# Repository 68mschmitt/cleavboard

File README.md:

# Cleaver keyboard

A keyboard for my best tantrum buddy Cleaver: 117 hot-swap MX keys, with RGB and
single-color lighting variants.

## Current revision: 0.11

**[PCB fabrication package](designs/module-rp2040/manufacturing/rev0.11/README.md)** ·
**[Case, switch plate and assembly guide](designs/module-rp2040/mechanical/rev0.11/README.md)**

The PCB screws to the underside of the switch plate, then the combined assembly
slides over tall base posts and screws into the base. A replaceable USB-C bezel
lets the cable opening be fitted after assembling the actual controller.
The case retains its lower 3° profile, hidden cover screws and captured badge.
Use the **rev0.11 PCB, plate, base and cover together**.

## Revision 0.9 showcase (historical)

The earlier **[rev0.9](designs/module-rp2040/manufacturing/rev0.9/README.md)** introduced a
**2 × 1 inch [replaceable illuminated logo](designs/module-rp2040/LOGO.md)** between
the front three-key clusters, with matching rectangular plate/cover openings
and an 8 mm deeper front bezel.

Rendered from the actual rev0.9 case, populated PCB, switch plate and removable
badge, with all 117 switches, modeled keycaps, stabilizers and mounting hardware.
Colors, keycap profiles and logo illumination are illustrative; the sample “C”
glows cyan while per-key RGB is off.
[Full-resolution render and reproduction details](designs/module-rp2040/mechanical/rev0.9/case/renderings/README.md).

| Feature | Revision 0.9 |
| --- | --- |
| Layout | 117 keys: full-size typing area, numpad, navigation/arrow cluster, left macro column and extra front macro keys |
| Switches | Hot-swap MX, Cherry-compatible **plate-mount stabilizers**, 6.25u spacebar |
| Controller | **Waveshare RP2040-Plus 4MB**, removable via underside SMT sockets; right-facing USB-C |
| Lighting | **117 per-key + 4 logo RGB LEDs**, reverse-mounted; protected USB LED supply |
| Replaceable logo | **50.8 × 25.4 mm badge**, printed light well, 51.2 × 25.8 mm plate/cover openings; QMK/Vial color control |
| Firmware | **QMK / Vial**, with key remapping, macros and RGB control; default and Vial UF2 builds included |
| Enclosure | **5° rear-raised case**, 11 M2 PCB standoffs, controller-socket backstops, removable cover and USB-C opening |
| Dimensions | PCB: **452.44 × 147.64 × 1.6 mm**; case base: approximately **466 × 172 mm** |

### Build and explore

- **Current mechanics:** [rev0.11 cartridge and USB bezel](designs/module-rp2040/mechanical/rev0.11/README.md),
  including STL/STEP, FreeCAD assembly, mounting plan and fit coupons.
- **Electronics:** [design and assembly guide](designs/module-rp2040/README.md),
  [rev0.11 fabrication package, BOM and placement files](designs/module-rp2040/manufacturing/rev0.11/README.md).
- **Earlier mechanics:** [rev0.10 case for the rev0.9 PCB](designs/module-rp2040/mechanical/rev0.10/README.md).
- **Firmware:** [ready-to-flash UF2 files and instructions](designs/module-rp2040/manufacturing/rev0.9/firmware/README.md),
  [firmware source and configuration](designs/module-rp2040/firmware/README.md).
- **Look inside:** [populated PCB previews](designs/module-rp2040/previews/README.md),
  [current mounting plan](designs/module-rp2040/mechanical/rev0.11/case/mounting-plan.svg),
  [recorded validation and remaining prototype checks](designs/module-rp2040/VALIDATION.md).

> **Prototype status:** Electrical/layout checks and firmware builds have recorded
> passing results; physical hardware operation and case fit remain unverified.
> Print the fit coupons first. The case and plate are full-size, unsplit parts;
> the case needs approximately a 466 × 175 mm print area **plus brim clearance**.
> Use the specified long module headers and matching rev0.11 PCB/base/plate/cover. JLCPCB
> engineering/placement approval and physical socket mating remain required.

## Choose a hardware design

| Design | Open in KiCad | Documentation |
| --- | --- | --- |
| **Module RP2040 — rev0.11:** socketed RP2040-Plus, removable PCB/plate cartridge, adjustable USB bezel and illuminated badge | [Cleaver.kicad_pro](designs/module-rp2040/Cleaver.kicad_pro) | [Design and assembly](designs/module-rp2040/README.md), [manufacturing](designs/module-rp2040/manufacturing/README.md) |
| **Embedded RP2040 — embedded-0.2:** onboard RP2040 and USB-C, per-key RGB | [Cleaver-Embedded.kicad_pro](designs/embedded-rp2040/Cleaver-Embedded.kicad_pro) | [Design and status](designs/embedded-rp2040/README.md), [handoff](designs/embedded-rp2040/HANDOFF.md) |
| **Single-color devboard — white-0.1:** YD-RP2040 module, white backlight | [Cleaver-White.kicad_pro](designs/single-color-devboard/Cleaver-White.kicad_pro) | [Design and status](designs/single-color-devboard/README.md), [manufacturing](designs/single-color-devboard/manufacturing/README.md) |

Each design owns its KiCad libraries, firmware, generation tools, validation,
and manufacturing files. Read its documentation for revision and prototype status.

## Repository layout

```text
assets/                        Shared layout inputs and silkscreen artwork
designs/
  module-rp2040/               Original RGB module design, mechanics and releases
  embedded-rp2040/             Integrated-controller RGB design
  single-color-devboard/       Module-based white-backlight design
docs/                          Repository organization and path migration guide
tools/                         Cross-design utilities and repository checks
```

- [Design comparison](designs/README.md)
- [Repository structure and file-placement conventions](docs/REPOSITORY.md)
- [Original keyboard layout](assets/layout/README.md)
- [Taviana artwork, previews and recorded checks](assets/artwork/taviana/README.md)
- [Tools and verification commands](tools/README.md)

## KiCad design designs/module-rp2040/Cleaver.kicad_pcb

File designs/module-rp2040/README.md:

# Cleaver PCB — revision 0.11

**New: [replaceable illuminated logo](LOGO.md)** between M6–M8 and M9–M11.
Four RGB LEDs illuminate a **50.8 × 25.4 mm (2 × 1 inch)** printed badge through
matching **51.2 × 25.8 mm** plate/cover openings. The front bezel and plate extend
8 mm forward, preserving key positions. The light well and flanged insert lift
out when the cover is removed. The 121-pixel rev0.9 firmware remains compatible.

**New mounting arrangement:** use the [rev0.11 PCB, switch plate, base and cover](mechanical/rev0.11/README.md)
together. Twelve large PCB holes pass over tall base posts; twelve separate
underside screws attach the PCB to downward plate bosses. The assembled cartridge
then screws to the base from above. A replaceable USB bezel is fitted after
measuring the actual controller. The lower 3° profile, hidden cover screws and
anti-rattle badge retention carry forward.

**Taviana Tactical artwork:** the active PCB includes a 34 mm-wide top-side logo.
Use the current [revision 0.11 fabrication files](manufacturing/rev0.11/).

117 MX hot-swap switches, 121 reverse-mount RGB LEDs, and the **Waveshare
RP2040-Plus 4MB USB-C module** (bare SKU 20290), plugged into underside SMT
bottom-entry sockets. The keyboard is
USB-powered, with **no mechanical power switch** and no separate power supply.

Read [VALIDATION.md](VALIDATION.md) for the recorded checks and remaining prototype
tests. The old [DESIGN_REVIEW.md](DESIGN_REVIEW.md) describes revision 0.2, not this
replacement design. Electrical checks do not substitute for a physical prototype
or final plate/case checks.

**Revision 0.11 manufacturing:** all **489 factory-populated parts are underside
SMD**, including C5, the HanElectricity hot-swap sockets and **J1/J2 Harwin
M20-7862042 controller sockets**. U1 plugs in from above through 40 **NPTH**
holes. Solder two **Samtec TSW-120-14-G-S** strips to the module only: 8.13 mm
posts down, 2.79 mm tails through the module. Stock pre-headered SKU 20808 is
**not qualified**. See the [socket drawing, pin budget and production gates](references/CONTROLLER-SOCKETS-0.7.md).
TP1 is a bare underside VBUS test pad.
There are **twelve Ø7 mm post passages and twelve Ø2.2 mm attachment holes**,
five labelled underside probe pads and three bottom fiducials.
Use [`manufacturing/rev0.11/`](manufacturing/rev0.11/) for the purchasing BOM,
corrected socket placement data and fabrication package; use
[`mechanical/`](mechanical/) for the matching stabilizer/switch plate and
case mounting references. **Allow 11 mm clearance under C5**; the old case-depth
assumption no longer applies there. The [rev0.11 case base](mechanical/rev0.11/case/README.md)
includes socket-insertion backstops. Older Gerbers and placement exports are not
this revision. Original-part evidence remains in the [component review](references/COMPONENT-REVIEW.md);
new socket evidence is linked above. Supplier DFM and physical mating remain open.

## USB LED power through pin 40

The Waveshare **pin 40 is raw USB VBUS**, connected directly to the USB-C power
pins ahead of its VSYS isolation diode. A **0.6 mm PCB route** connects J2.1 (U1.40) to
the existing protected LED branch. **No module modification or tap wire is needed.**
TP1 at `(446, 27)` mm is retained as a VBUS test pad; TP3 measures the same net.
Ground returns through the module's ordinary GND header pins.

Use an RP2040-Plus for this revision: the former YD-RP2040 has diode-fed Vout at
pin 40 and is not a suitable substitute. Leave the Waveshare battery connector
unused for this USB-only keyboard.

LED power path:

```text
Module USB VBUS pin 40 → carrier copper → F1 (0.50 A PTC) → U3 (TPS2553) → LED_5V
Module GPIO28 → U3 enable (100 kΩ default-off pull-down)
Module GPIO27 → U2 level translator → R1 (330 Ω) → first LED DIN
```

- U3's **75 kΩ, 1%** current-limit resistor gives approximately **353 mA nominal**
  LED-branch current limiting (about **311–401 mA** using the datasheet bounds and
  resistor tolerance). This is separate from the module's own consumption.
- Firmware caps key brightness at **8/255**, with four badge pixels capped at
  **32/255**. For 12 mA/colour LEDs, combined full-white colour current is
  approximately **150.2 mA**, plus LED idle current and MCU
  consumption. Measure the actual total; a brightness setting or USB descriptor is
  not itself a current measurement. Do not raise the cap casually.
- RGB power stays off until USB is configured, and is removed on suspend and when
  RGB Matrix is disabled. R2 keeps it off during reset/bootloader operation.
- Every LED has its own 100 nF capacitor. C2 is 22 µF; **C5 is a low-impedance
  470 µF reservoir after the current limiter**, to supply coincident LED PWM pulses.
  It is not attached directly across USB at cable insertion. Fit its polarity
  correctly: pad 1 / `+` is positive, and the can's negative mark goes to pad 2.
- U2 is **SN74LV1T125DBVR**, not an arbitrary 74LVC/HC/AHCT substitute. Its
  reduced input thresholds translate 3.3 V data to the LED supply, and its input
  tolerates the GPIO while the LED supply is off.
- TP1 is connected to USB VBUS, not a separate power input.

## Controller placement and pinout

The module uses two 20-pin, 2.54 mm-pitch headers **17.78 mm apart**. Its body is
**51 × 21 mm**, based on Waveshare's mechanical drawing. It sits
top-right, USB-C facing the right edge. Header centres are retained from rev0.5;
the smaller body ends **1.17 mm inside** the carrier edge, with the USB-C shell
projecting beyond the module body. Use headers/sockets with sufficient
underside clearance, and confirm the actual purchased board against a 1:1 print.

The module uses **Pico-compatible numbering**, not alternating 2×20 numbering.
J1.1–20 carry module pins 1–20; **J2.1–20 carry module pins 40–21**, respectively.
The 7.5 mm female socket bodies sit below the carrier; male-header insulators
seat on top. The module is not raised by a top-side female header stack.

| Module pin | RP2040-Plus function | Carrier use |
| --- | --- | --- |
| 35 | ADC_VREF | Unconnected |
| 36 | 3V3_OUT | Unconnected |
| 37 | 3V3_EN | Unconnected; module pull-up keeps regulator enabled |
| 38 | GND | Ground plane |
| 39 | VSYS | Unconnected |
| 40 | USB VBUS | RAW_USB_5V → F1 → U3 → LED_5V |

The module's BOOT and RESET buttons remain accessible in the upper-right area.
No separate USB connector or USB data traces are required on the carrier.

## Matrix, RGB order, and assembly

The electrical matrix is **8×16 ROW2COL**, with 117 unique populated cells:

| Function | GPIOs |
| --- | --- |
| Rows 0–7 | GP0–GP7 |
| Columns 0–15 | GP8–GP22, GP26 |
| RGB data | GP27 |
| RGB power enable | GP28 |

Logical rows are banks of 16 switches in KLE order, **not** the seven physical
key rows. This avoids the old duplicate addresses without adding an expander.
Vial still displays the original physical layout. Every switch goes from its row
through the switch to the diode anode; the cathode connects to the column.

- Diodes are **1N4148W, SOD-123**, using normal **pad 1 = cathode, pad 2 = anode**
  numbering. Match the diode's stripe to the footprint's cathode mark.
  Diodes sit 8.25 mm above switch centres, improving body clearance to sockets.
  These and all other SMD parts are factory-assembled underneath.
- LEDs use the **OPSCO SK6812MINI-E / C5149201 catalog pinout**:
  **1=GND, 2=DIN, 3=VDD, 4=DOUT**. This renumbers the older Rev.02 sheet's pins
  without changing physical net positions. Do not substitute MINI/EA/5050
  packages based only on a similar name.
- LEDs and their 0805 bypass capacitors are on **B.Cu**, with emitters facing
  through the **3.6 × 3.2 mm PCB openings toward the switches**. These are real
  Edge.Cuts, not reference artwork. Mounting pads are outside the opening and
  retain at least 0.5 mm nominal edge clearance.
  From the **top/emitter side**, pad 3 is upper-left, pad 4 lower-left, pad 1
  lower-right, and pad 2 upper-right. The ground-corner mark is on the back.
  Check this orientation on one LED before assembling the entire chain.
  Specify an internal milling-corner radius **no larger than 0.5 mm** (prefer
  0.4 mm) for these small openings; a default 2 mm-diameter cutter will not fit
  the LED's square corners. Confirm the fabricator's aperture tolerances.
- The chain begins at the function-row Pause key near the MCU circuitry, runs
  left across that row, and then snakes across subsequent physical rows. Firmware
  entries are in **actual chain order**, not switch-reference order.
  LED118–LED121 append after LED112 (M6), at indices 117–120, and illuminate the
  badge. C218–C221 are their bypass capacitors. [Badge circuit and controls](LOGO.md#rgb-and-power).
- `firmware/key_matrix.csv` gives switch, matrix cell, position, and RGB index.
  `manufacturing/BOM.csv` lists exact references, values, board side, and placement coordinates.
  SWxxx, Dxxx, and LEDxxx refer to the same physical key; C101 belongs to SW001.
  Each SW footprint is a **B.Cu HanElectricity CPG151101S11-16 / C41430893 socket**.
  The switch plugs in from above. Its origin is still the switch centre; use the
   revision-specific factory CPL for the actual socket placement centre. The owner
   provides the bare RP2040-Plus and two **TSW-120-14-G-S** male strips, soldered
   only to the module. J1/J2 female sockets are factory-fitted underneath.
   Leave all carrier entry holes open and solder-free.
- Caps/Num/Scroll lock are indicated using their **own keys' RGB LEDs**. The three
  decorative KLE circles above the numpad do not represent additional components
hidden beneath the MCU.

The four-layer stack uses In1.Cu as ground return, with explicit ground vias
outside solder pads. A **switched LED_5V pour on F.Cu** and off-pad power vias
feed each LED and bypass capacitor, avoiding a narrow, serial supply chain.
Signals use F.Cu/In2.Cu/B.Cu. Preferred track widths are
0.3 mm for signals and 0.6 mm for power; manufacturing minima remain 0.2 mm track,
0.2 mm clearance, 0.5 mm copper-to-edge, and the existing project hole rules.
Ordinary through-vias are used; filled/capped via-in-pad fabrication is not needed.

The power/buffer circuit and bulk capacitor occupy the empty region **left of
the MCU**, rather than overlapping its body or headers. C5 is a bottom-mounted
**Nichicon PCF1A471MCL1GS / C3275369**, 470 µF/10 V SMD polymer, Ø10 mm and
10 mm maximum height, centred at `(377, 6)` mm. Allow **11 mm free case depth
below the PCB at C5**. The old top capacitor plate opening can remain unused.

**Mechanical interface:** switch centres and board outline are retained. The
new plate in `mechanical/` includes matching M2 holes and Cherry-style
**plate-mount stabilizers**: seven 2u sets and one 6.25u spacebar set. Do not use
PCB-mount stabilizers. The custom printed case uses the supplied hole-coordinate
table and 6 mm screw/standoff envelopes. See the mechanical README for nominal
plate spacing, clip thickness, controller/capacitor openings and a fit coupon.

## Populated 3D view

Open **Cleaver.kicad_pcb → View → 3D Viewer (Alt+3)**. The project includes local
models for **all 490 populated/modelled footprints**, including front-side MX switches,
back-side sockets, LEDs/passives, and a simplified RP2040-Plus with long headers/USB-C.
The controller sockets have nominal supplier-dimensioned STEP/VRML models.
No extra model-library installation is needed. Flip the view with **F** to see
the underside. TP1–TP6, mounting holes and fiducials intentionally have no models.

- [Historical rev0.7 top-side preview](previews/Cleaver-rev0.7-top.png)
- [Historical rev0.7 bottom-side preview](previews/Cleaver-rev0.7-bottom.png)
- [Model coverage, approximations, licensing, and STEP export](Cleaver.3dshapes/README.md)

The module/header stack and some package details are approximations; keycaps,
plate, stabilizers, and case are not modeled. These views do not replace the
physical fit checks above. Model assignments are preserved by the generator.

## Vial-QMK firmware

Pin assignments are unchanged; revision 0.9 builds drive all 121 LEDs. Images and
instructions are in [`manufacturing/rev0.9/firmware/`](manufacturing/rev0.9/firmware/).

Copy `firmware/` to `keyboards/cleaver/` in a **vial-qmk** checkout. From that
checkout run:

```sh
make cleaver:default
make cleaver:vial
```

The Vial keymap includes its own UID, physical `vial.json`, VIA/Vial/VialRGB rules,
and a secure **Esc + main Enter** unlock combination. No insecure-unlock option is
enabled. The RP2040 vendor/PIO WS2812 driver uses GRB data and explicit timings.
The module's onboard GP25 status LED is not included in the keyboard's 121-LED chain.
Default macro-key assignments can be changed in Vial.

All 26 carrier GPIOs retain their physical pin numbers. The Vial UID, VID/PID,
layout, unlock combination, first 117 RGB indices and USB-aware GP28 power control
are retained. Four non-key badge pixels extend the chain. QMK's default
W25Q080-compatible boot stage supports the module's
W25Q32JV flash. EEPROM remains explicitly within the first 2MB, also valid on
the 16MB RP2040-Plus variant. See [`firmware/README.md`](firmware/README.md).

Build provenance and the tested vial-qmk commit belong in [VALIDATION.md](VALIDATION.md).
Compiled firmware has not been exercised on a physical keyboard by this agent.

## Regeneration and checks

`source/design.py` is the shared source for schematic, PCB nets, matrix, RGB
order, and firmware. The PCB receives pad nets from **KiCad's exported schematic
netlist**. Regeneration preserves project settings except for the explicit power
netclass and the preferred 0.3 mm signal width; it does not weaken DRC minima.

Run the following commands from the repository root with KiCad's Python environment.

Generate a fresh **unrouted** placement and DSN only when deliberately restarting
routing:

```sh
python3 -B designs/module-rp2040/source/generate_kicad.py --placement-only
```

Import a matching routed Specctra session:

```sh
python3 -B designs/module-rp2040/source/generate_kicad.py --ses designs/module-rp2040/routing/Cleaver.ses
python3 -B designs/module-rp2040/source/check_kicad.py
python3 -B -m unittest discover -s designs/module-rp2040/source -p 'test_*.py'
```

See `routing/README.md` for the autorouter invocation. The DSN preparation carries
KiCad's edge clearances and power widths into the router; a router reporting
“0 violations” is **not** a substitute for KiCad DRC after session import.

## Hardware sources

- [Waveshare RP2040-Plus documentation](https://docs.waveshare.com/RP2040-Plus).
- [Archived module schematic](references/RP2040-Plus-schematic.pdf),
  [dimension drawing](references/RP2040-Plus-dimensions.webp), and
  [source/pinout review](references/RP2040-Plus.md).
- [OPSCO C5149201 datasheet](https://datasheet.lcsc.com/datasheet/pdf/0907a34a701b4aef568078003f6e9eae.pdf).
  Physical reverse-mount signal orientation also agrees with the
  [established MX MINI-E footprint](https://github.com/ebastler/kicad-keyboard-parts.pretty/blob/master/MX_SK6812MINI-E.kicad_mod).
- [SN74LV1T125](https://www.ti.com/lit/ds/symlink/sn74lv1t125.pdf),
  [TPS2553](https://www.ti.com/lit/ds/symlink/tps2553.pdf), and
  [Nichicon PCF capacitor specification](references/Nichicon-PCF.pdf).
- [Exact-part JLCPCB review and socket compatibility](references/COMPONENT-REVIEW.md).

Fit the carrier to its socket-support base **before inserting U1**; the 40
contacts can require substantial force. Withdraw evenly, never by levering the
USB shell. Print the new USB/seat coupons first.

Bring up the prototype on current-limited USB power: check supply polarity/shorts,
test the module and one key first, then one LED, all 117 keys (including chords),
the complete RGB chain, maximum allowed full-white current/rail ripple,
suspend/resume, and USB-A-to-C plus C-to-C enumeration. Keep the brightness cap
until those measurements pass.

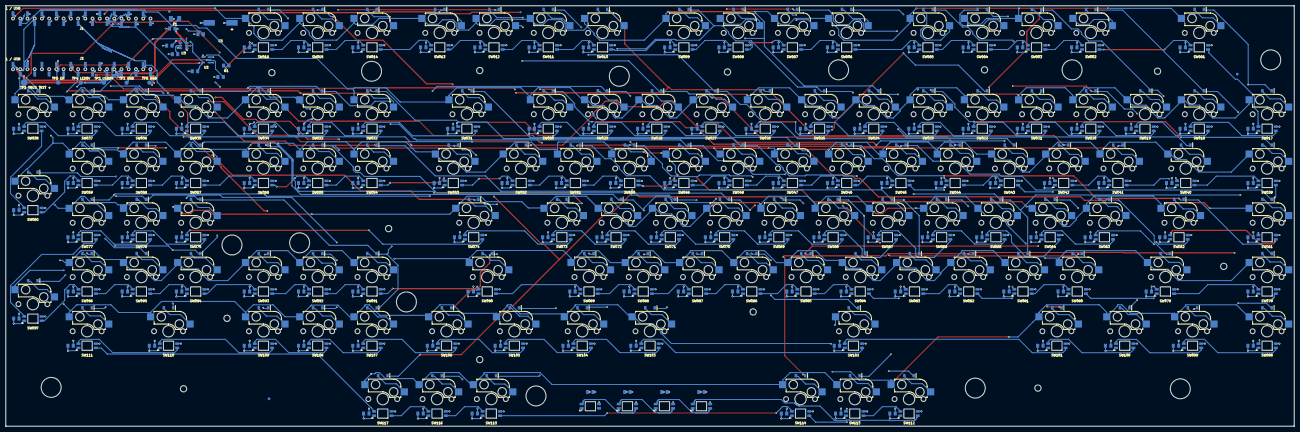
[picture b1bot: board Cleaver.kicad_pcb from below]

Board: 4 copper layers, 452.4 x 147.6 mm, 524 parts (498 on the bottom side), 270 nets.

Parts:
C1: 1uF 50V X7R; C_0805
C2: 22uF 10V X5R; C_0805
C3, C101, C102, C103, C104, C105, C106, C107, C108, C109, C110, C111, C112, C113, C114, C115, C116, C117, C118, C119, C120, C121, C122, C123, C124, C125, C126, C127, C128, C129, C130, C131, C132, C133, C134, C135, C136, C137, C138, C139, C140, C141, C142, C143, C144, C145, C146, C147, C148, C149, C150, C151, C152, C153, C154, C155, C156, C157, C158, C159, C160, C161, C162, C163, C164, C165, C166, C167, C168, C169, C170, C171, C172, C173, C174, C175, C176, C177, C178, C179, C180, C181, C182, C183, C184, C185, C186, C187, C188, C189, C190, C191, C192, C193, C194, C195, C196, C197, C198, C199, C200, C201, C202, C203, C204, C205, C206, C207, C208, C209, C210, C211, C212, C213, C214, C215, C216, C217, C218, C219, C220, C221: 100nF 50V X7R; C_0805
C5: 470uF 10V PCF1A471MCL1GS; C_PCF_D10
D001, D002, D003, D004, D005, D006, D007, D008, D009, D010, D011, D012, D013, D014, D015, D016, D017, D018, D019, D020, D021, D022, D023, D024, D025, D026, D027, D028, D029, D030, D031, D032, D033, D034, D035, D036, D037, D038, D039, D040, D041, D042, D043, D044, D045, D046, D047, D048, D049, D050, D051, D052, D053, D054, D055, D056, D057, D058, D059, D060, D061, D062, D063, D064, D065, D066, D067, D068, D069, D070, D071, D072, D073, D074, D075, D076, D077, D078, D079, D080, D081, D082, D083, D084, D085, D086, D087, D088, D089, D090, D091, D092, D093, D094, D095, D096, D097, D098, D099, D100, D101, D102, D103, D104, D105, D106, D107, D108, D109, D110, D111, D112, D113, D114, D115, D116, D117: 1N4148W; D_SOD123
F1: 1206L050YR 0.50A hold; PTC_1206
FID1, FID2, FID3: Fiducial
H1, H2, H3, H4, H5, H6, H7, H8, H9, H10, H11, H12: MountingHole_Post7
H13, H14, H15, H16, H17, H18, H19, H20, H21, H22, H23, H24: MountingHole_M2
J1, J2: M20-7862042; Harwin_M20_7862042
LED001, LED002, LED003, LED004, LED005, LED006, LED007, LED008, LED009, LED010, LED011, LED012, LED013, LED014, LED015, LED016, LED017, LED018, LED019, LED020, LED021, LED022, LED023, LED024, LED025, LED026, LED027, LED028, LED029, LED030, LED031, LED032, LED033, LED034, LED035, LED036, LED037, LED038, LED039, LED040, LED041, LED042, LED043, LED044, LED045, LED046, LED047, LED048, LED049, LED050, LED051, LED052, LED053, LED054, LED055, LED056, LED057, LED058, LED059, LED060, LED061, LED062, LED063, LED064, LED065, LED066, LED067, LED068, LED069, LED070, LED071, LED072, LED073, LED074, LED075, LED076, LED077, LED078, LED079, LED080, LED081, LED082, LED083, LED084, LED085, LED086, LED087, LED088, LED089, LED090, LED091, LED092, LED093, LED094, LED095, LED096, LED097, LED098, LED099, LED100, LED101, LED102, LED103, LED104, LED105, LED106, LED107, LED108, LED109, LED110, LED111, LED112, LED113, LED114, LED115, LED116, LED117, LED118, LED119, LED120, LED121: SK6812MINI-E C5149201; MINI_E
LOGO1: TavianaTactical_34mm
R1: 330R; R_0805
R2, R3: 100k; R_0805
R4: 75k 1%; R_0805
SW001, SW002, SW003, SW004, SW005, SW006, SW007, SW008, SW009, SW010, SW011, SW012, SW013, SW014, SW015, SW016, SW017, SW018, SW019, SW020, SW021, SW022, SW023, SW024, SW025, SW026, SW027, SW028, SW029, SW030, SW031, SW032, SW033, SW034, SW035, SW036, SW037, SW038, SW039, SW040, SW041, SW042, SW043, SW044, SW045, SW046, SW047, SW048, SW049, SW050, SW051, SW052, SW053, SW054, SW055, SW056, SW057, SW058, SW059, SW060, SW061, SW062, SW063, SW064, SW065, SW066, SW067, SW068, SW069, SW070, SW071, SW072, SW073, SW074, SW075, SW076, SW077, SW078, SW079, SW080, SW081, SW082, SW083, SW084, SW085, SW086, SW087, SW088, SW089, SW090, SW091, SW092, SW093, SW094, SW095, SW096, SW097, SW098, SW099, SW100, SW101, SW102, SW103, SW104, SW105, SW106, SW107, SW108, SW109, SW110, SW111, SW112, SW113, SW114, SW115, SW116, SW117: CPG151101S11-16; HanElectricity_CPG151101S11-16
TP1: USB VBUS TEST +5V; WirePad
TP2: GND; TestPad
TP3: RAW_USB_5V; TestPad
TP4: LED_5V; TestPad
TP5: LED_EN; TestPad
TP6: RGB_BUFFERED; TestPad
U1: Waveshare RP2040-Plus 4MB; Waveshare_RP2040_Plus
U2: SN74LV1T125DBVR; LV1T125
U3: TPS2553DBVR; TPS2553

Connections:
/COL00: D001.1, D017.1, D033.1, D049.1, D065.1, D081.1, D097.1, D113.1, J1.11
/COL01: D002.1, D018.1, D034.1, D050.1, D066.1, D082.1, D098.1, D114.1, J1.12
/COL02: D003.1, D019.1, D035.1, D051.1, D067.1, D083.1, D099.1, D115.1, J1.14
/COL03: D004.1, D020.1, D036.1, D052.1, D068.1, D084.1, D100.1, D116.1, J1.15
/COL04: D005.1, D021.1, D037.1, D053.1, D069.1, D085.1, D101.1, D117.1, J1.16
/COL05: D006.1, D022.1, D038.1, D054.1, D070.1, D086.1, D102.1, J1.17
/COL06: D007.1, D023.1, D039.1, D055.1, D071.1, D087.1, D103.1, J1.19
/COL07: D008.1, D024.1, D040.1, D056.1, D072.1, D088.1, D104.1, J1.20
/COL08: D009.1, D025.1, D041.1, D057.1, D073.1, D089.1, D105.1, J2.20
/COL09: D010.1, D026.1, D042.1, D058.1, D074.1, D090.1, D106.1, J2.19
/COL10: D011.1, D027.1, D043.1, D059.1, D075.1, D091.1, D107.1, J2.17
/COL11: D012.1, D028.1, D044.1, D060.1, D076.1, D092.1, D108.1, J2.16
/COL12: D013.1, D029.1, D045.1, D061.1, D077.1, D093.1, D109.1, J2.15
/COL13: D014.1, D030.1, D046.1, D062.1, D078.1, D094.1, D110.1, J2.14
/COL14: D015.1, D031.1, D047.1, D063.1, D079.1, D095.1, D111.1, J2.12
/COL15: D016.1, D032.1, D048.1, D064.1, D080.1, D096.1, D112.1, J2.10
/CURRENT_LIMIT: R4.1, U3.5
/FUSED_5V: C1.1, F1.2, U3.1
/GND: C1.2, C2.2, C3.2, C5.2, C101.2, C102.2, C103.2, C104.2, C105.2, C106.2, C107.2, C108.2, C109.2, C110.2, C111.2, C112.2, C113.2, C114.2, C115.2, C116.2, C117.2, C118.2, C119.2, C120.2, C121.2, C122.2, C123.2, C124.2, C125.2, C126.2, C127.2, C128.2, C129.2, C130.2, C131.2, C132.2, C133.2, C134.2, C135.2, C136.2, C137.2, C138.2, C139.2, C140.2, C141.2, C142.2, C143.2, C144.2, C145.2, C146.2, C147.2, C148.2, C149.2, C150.2, C151.2, C152.2, C153.2, C154.2, C155.2, C156.2, C157.2, C158.2, C159.2, C160.2, C161.2, C162.2, C163.2, C164.2, C165.2, C166.2, C167.2, C168.2, C169.2, C170.2, C171.2, C172.2, C173.2, C174.2, C175.2, C176.2, C177.2, C178.2, C179.2, C180.2, C181.2, C182.2, C183.2, C184.2, C185.2, C186.2, C187.2, C188.2, C189.2, C190.2, C191.2, C192.2, C193.2, C194.2, C195.2, C196.2, C197.2, C198.2, C199.2, C200.2, C201.2, C202.2, C203.2, C204.2, C205.2, C206.2, C207.2, C208.2, C209.2, C210.2, C211.2, C212.2, C213.2, C214.2, C215.2, C216.2, C217.2, C218.2, C219.2, C220.2, C221.2, J1.3, J1.8, J1.13, J1.18, J2.3, J2.8, J2.13, J2.18, LED001.1, LED002.1, LED003.1, LED004.1, LED005.1, LED006.1, LED007.1, LED008.1, LED009.1, LED010.1, LED011.1, LED012.1, LED013.1, LED014.1, LED015.1, LED016.1, LED017.1, LED018.1, LED019.1, LED020.1, LED021.1, LED022.1, LED023.1, LED024.1, LED025.1, LED026.1, LED027.1, LED028.1, LED029.1, LED030.1, LED031.1, LED032.1, LED033.1, LED034.1, LED035.1, LED036.1, LED037.1, LED038.1, LED039.1, LED040.1, LED041.1, LED042.1, LED043.1, LED044.1, LED045.1, LED046.1, LED047.1, LED048.1, LED049.1, LED050.1, LED051.1, LED052.1, LED053.1, LED054.1, LED055.1, LED056.1, LED057.1, LED058.1, LED059.1, LED060.1, LED061.1, LED062.1, LED063.1, LED064.1, LED065.1, LED066.1, LED067.1, LED068.1, LED069.1, LED070.1, LED071.1, LED072.1, LED073.1, LED074.1, LED075.1, LED076.1, LED077.1, LED078.1, LED079.1, LED080.1, LED081.1, LED082.1, LED083.1, LED084.1, LED085.1, LED086.1, LED087.1, LED088.1, LED089.1, LED090.1, LED091.1, LED092.1, LED093.1, LED094.1, LED095.1, LED096.1, LED097.1, LED098.1, LED099.1, LED100.1, LED101.1, LED102.1, LED103.1, LED104.1, LED105.1, LED106.1, LED107.1, LED108.1, LED109.1, LED110.1, LED111.1, LED112.1, LED113.1, LED114.1, LED115.1, LED116.1, LED117.1, LED118.1, LED119.1, LED120.1, LED121.1, R2.2, R3.2, R4.2, TP2.1, U2.1, U2.3, U3.2
/KEY000: D001.2, SW001.2
/KEY001: D002.2, SW002.2
/KEY002: D003.2, SW003.2
/KEY003: D004.2, SW004.2
/KEY004: D005.2, SW005.2
/KEY005: D006.2, SW006.2
/KEY006: D007.2, SW007.2
/KEY007: D008.2, SW008.2
/KEY008: D009.2, SW009.2
/KEY009: D010.2, SW010.2
/KEY010: D011.2, SW011.2
/KEY011: D012.2, SW012.2
/KEY012: D013.2, SW013.2
/KEY013: D014.2, SW014.2
/KEY014: D015.2, SW015.2
/KEY015: D016.2, SW016.2
/KEY016: D017.2, SW017.2
/KEY017: D018.2, SW018.2
/KEY018: D019.2, SW019.2
/KEY019: D020.2, SW020.2
/KEY020: D021.2, SW021.2
/KEY021: D022.2, SW022.2
/KEY022: D023.2, SW023.2
/KEY023: D024.2, SW024.2
/KEY024: D025.2, SW025.2
/KEY025: D026.2, SW026.2
/KEY026: D027.2, SW027.2
/KEY027: D028.2, SW028.2
/KEY028: D029.2, SW029.2
/KEY029: D030.2, SW030.2
/KEY030: D031.2, SW031.2
/KEY031: D032.2, SW032.2
/KEY032: D033.2, SW033.2
/KEY033: D034.2, SW034.2
/KEY034: D035.2, SW035.2
/KEY035: D036.2, SW036.2
/KEY036: D037.2, SW037.2
/KEY037: D038.2, SW038.2
/KEY038: D039.2, SW039.2
/KEY039: D040.2, SW040.2
/KEY040: D041.2, SW041.2
/KEY041: D042.2, SW042.2
/KEY042: D043.2, SW043.2
/KEY043: D044.2, SW044.2
/KEY044: D045.2, SW045.2
/KEY045: D046.2, SW046.2
/KEY046: D047.2, SW047.2
/KEY047: D048.2, SW048.2
/KEY048: D049.2, SW049.2
/KEY049: D050.2, SW050.2
/KEY050: D051.2, SW051.2
/KEY051: D052.2, SW052.2
/KEY052: D053.2, SW053.2
/KEY053: D054.2, SW054.2
/KEY054: D055.2, SW055.2
/KEY055: D056.2, SW056.2
/KEY056: D057.2, SW057.2
/KEY057: D058.2, SW058.2
/KEY058: D059.2, SW059.2
/KEY059: D060.2, SW060.2
/KEY060: D061.2, SW061.2
/KEY061: D062.2, SW062.2
/KEY062: D063.2, SW063.2
/KEY063: D064.2, SW064.2
/KEY064: D065.2, SW065.2
/KEY065: D066.2, SW066.2
/KEY066: D067.2, SW067.2
/KEY067: D068.2, SW068.2
/KEY068: D069.2, SW069.2
/KEY069: D070.2, SW070.2
/KEY070: D071.2, SW071.2
/KEY071: D072.2, SW072.2
/KEY072: D073.2, SW073.2
/KEY073: D074.2, SW074.2
/KEY074: D075.2, SW075.2
/KEY075: D076.2, SW076.2
/KEY076: D077.2, SW077.2
/KEY077: D078.2, SW078.2
/KEY078: D079.2, SW079.2
/KEY079: D080.2, SW080.2
/KEY080: D081.2, SW081.2
/KEY081: D082.2, SW082.2
/KEY082: D083.2, SW083.2
/KEY083: D084.2, SW084.2
/KEY084: D085.2, SW085.2
/KEY085: D086.2, SW086.2
/KEY086: D087.2, SW087.2
/KEY087: D088.2, SW088.2
/KEY088: D089.2, SW089.2
/KEY089: D090.2, SW090.2
/KEY090: D091.2, SW091.2
/KEY091: D092.2, SW092.2
/KEY092: D093.2, SW093.2
/KEY093: D094.2, SW094.2
/KEY094: D095.2, SW095.2
/KEY095: D096.2, SW096.2
/KEY096: D097.2, SW097.2
/KEY097: D098.2, SW098.2
/KEY098: D099.2, SW099.2
/KEY099: D100.2, SW100.2
/KEY100: D101.2, SW101.2
/KEY101: D102.2, SW102.2
/KEY102: D103.2, SW103.2
/KEY103: D104.2, SW104.2
/KEY104: D105.2, SW105.2
/KEY105: D106.2, SW106.2
/KEY106: D107.2, SW107.2
/KEY107: D108.2, SW108.2
/KEY108: D109.2, SW109.2
/KEY109: D110.2, SW110.2
/KEY110: D111.2, SW111.2
/KEY111: D112.2, SW112.2
/KEY112: D113.2, SW113.2
/KEY113: D114.2, SW114.2
/KEY114: D115.2, SW115.2
/KEY115: D116.2, SW116.2
/KEY116: D117.2, SW117.2
/LED_5V: C2.1, C3.1, C5.1, C101.1, C102.1, C103.1, C104.1, C105.1, C106.1, C107.1, C108.1, C109.1, C110.1, C111.1, C112.1, C113.1, C114.1, C115.1, C116.1, C117.1, C118.1, C119.1, C120.1, C121.1, C122.1, C123.1, C124.1, C125.1, C126.1, C127.1, C128.1, C129.1, C130.1, C131.1, C132.1, C133.1, C134.1, C135.1, C136.1, C137.1, C138.1, C139.1, C140.1, C141.1, C142.1, C143.1, C144.1, C145.1, C146.1, C147.1, C148.1, C149.1, C150.1, C151.1, C152.1, C153.1, C154.1, C155.1, C156.1, C157.1, C158.1, C159.1, C160.1, C161.1, C162.1, C163.1, C164.1, C165.1, C166.1, C167.1, C168.1, C169.1, C170.1, C171.1, C172.1, C173.1, C174.1, C175.1, C176.1, C177.1, C178.1, C179.1, C180.1, C181.1, C182.1, C183.1, C184.1, C185.1, C186.1, C187.1, C188.1, C189.1, C190.1, C191.1, C192.1, C193.1, C194.1, C195.1, C196.1, C197.1, C198.1, C199.1, C200.1, C201.1, C202.1, C203.1, C204.1, C205.1, C206.1, C207.1, C208.1, C209.1, C210.1, C211.1, C212.1, C213.1, C214.1, C215.1, C216.1, C217.1, C218.1, C219.1, C220.1, C221.1, LED001.3, LED002.3, LED003.3, LED004.3, LED005.3, LED006.3, LED007.3, LED008.3, LED009.3, LED010.3, LED011.3, LED012.3, LED013.3, LED014.3, LED015.3, LED016.3, LED017.3, LED018.3, LED019.3, LED020.3, LED021.3, LED022.3, LED023.3, LED024.3, LED025.3, LED026.3, LED027.3, LED028.3, LED029.3, LED030.3, LED031.3, LED032.3, LED033.3, LED034.3, LED035.3, LED036.3, LED037.3, LED038.3, LED039.3, LED040.3, LED041.3, LED042.3, LED043.3, LED044.3, LED045.3, LED046.3, LED047.3, LED048.3, LED049.3, LED050.3, LED051.3, LED052.3, LED053.3, LED054.3, LED055.3, LED056.3, LED057.3, LED058.3, LED059.3, LED060.3, LED061.3, LED062.3, LED063.3, LED064.3, LED065.3, LED066.3, LED067.3, LED068.3, LED069.3, LED070.3, LED071.3, LED072.3, LED073.3, LED074.3, LED075.3, LED076.3, LED077.3, LED078.3, LED079.3, LED080.3, LED081.3, LED082.3, LED083.3, LED084.3, LED085.3, LED086.3, LED087.3, LED088.3, LED089.3, LED090.3, LED091.3, LED092.3, LED093.3, LED094.3, LED095.3, LED096.3, LED097.3, LED098.3, LED099.3, LED100.3, LED101.3, LED102.3, LED103.3, LED104.3, LED105.3, LED106.3, LED107.3, LED108.3, LED109.3, LED110.3, LED111.3, LED112.3, LED113.3, LED114.3, LED115.3, LED116.3, LED117.3, LED118.3, LED119.3, LED120.3, LED121.3, TP4.1, U2.5, U3.6
/LED_EN: J2.7, R2.1, TP5.1, U3.3
/RAW_USB_5V: F1.1, J2.1, TP1.1, TP3.1
/RGB_000: LED016.2, R1.2
/RGB_001: LED015.2, LED016.4
/RGB_002: LED014.2, LED015.4
/RGB_003: LED013.2, LED014.4
/RGB_004: LED012.2, LED013.4
/RGB_005: LED011.2, LED012.4
/RGB_006: LED010.2, LED011.4
/RGB_007: LED009.2, LED010.4
/RGB_008: LED008.2, LED009.4
/RGB_009: LED007.2, LED008.4
/RGB_010: LED006.2, LED007.4
/RGB_011: LED005.2, LED006.4
/RGB_012: LED004.2, LED005.4
/RGB_013: LED003.2, LED004.4
/RGB_014: LED002.2, LED003.4
/RGB_015: LED001.2, LED002.4
/RGB_016: LED001.4, LED017.2
/RGB_017: LED017.4, LED018.2
/RGB_018: LED018.4, LED019.2
/RGB_019: LED019.4, LED020.2
/RGB_020: LED020.4, LED021.2
/RGB_021: LED021.4, LED022.2
/RGB_022: LED022.4, LED023.2
/RGB_023: LED023.4, LED024.2
/RGB_024: LED024.4, LED025.2
/RGB_025: LED025.4, LED026.2
/RGB_026: LED026.4, LED027.2
/RGB_027: LED027.4, LED028.2
/RGB_028: LED028.4, LED029.2
/RGB_029: LED029.4, LED030.2
/RGB_030: LED030.4, LED031.2
/RGB_031: LED031.4, LED032.2
/RGB_032: LED032.4, LED033.2
/RGB_033: LED033.4, LED034.2
/RGB_034: LED034.4, LED035.2
/RGB_035: LED035.4, LED036.2
/RGB_036: LED036.4, LED037.2
/RGB_037: LED037.4, LED038.2
/RGB_038: LED038.4, LED060.2
/RGB_039: LED059.2, LED060.4
/RGB_040: LED058.2, LED059.4
/RGB_041: LED057.2, LED058.4
/RGB_042: LED056.2, LED057.4
/RGB_043: LED055.2, LED056.4
/RGB_044: LED054.2, LED055.4
/RGB_045: LED053.2, LED054.4
/RGB_046: LED052.2, LED053.4
/RGB_047: LED051.2, LED052.4
/RGB_048: LED050.2, LED051.4
/RGB_049: LED049.2, LED050.4
/RGB_050: LED048.2, LED049.4
/RGB_051: LED047.2, LED048.4
/RGB_052: LED046.2, LED047.4
/RGB_053: LED045.2, LED046.4
/RGB_054: LED044.2, LED045.4
/RGB_055: LED043.2, LED044.4
/RGB_056: LED042.2, LED043.4
/RGB_057: LED041.2, LED042.4
/RGB_058: LED040.2, LED041.4
/RGB_059: LED039.2, LED040.4
/RGB_060: LED039.4, LED061.2
/RGB_061: LED061.4, LED062.2
/RGB_062: LED062.4, LED063.2
/RGB_063: LED063.4, LED064.2
/RGB_064: LED064.4, LED065.2
/RGB_065: LED065.4, LED066.2
/RGB_066: LED066.4, LED067.2
/RGB_067: LED067.4, LED068.2
/RGB_068: LED068.4, LED069.2
/RGB_069: LED069.4, LED070.2
/RGB_070: LED070.4, LED071.2
/RGB_071: LED071.4, LED072.2
/RGB_072: LED072.4, LED073.2
/RGB_073: LED073.4, LED074.2
/RGB_074: LED074.4, LED075.2
/RGB_075: LED075.4, LED076.2
/RGB_076: LED076.4, LED077.2
/RGB_077: LED077.4, LED097.2
/RGB_078: LED096.2, LED097.4
/RGB_079: LED095.2, LED096.4
/RGB_080: LED094.2, LED095.4
/RGB_081: LED093.2, LED094.4
/RGB_082: LED092.2, LED093.4
/RGB_083: LED091.2, LED092.4
/RGB_084: LED090.2, LED091.4
/RGB_085: LED089.2, LED090.4
/RGB_086: LED088.2, LED089.4
/RGB_087: LED087.2, LED088.4
/RGB_088: LED086.2, LED087.4
/RGB_089: LED085.2, LED086.4
/RGB_090: LED084.2, LED085.4
/RGB_091: LED083.2, LED084.4
/RGB_092: LED082.2, LED083.4
/RGB_093: LED081.2, LED082.4
/RGB_094: LED080.2, LED081.4
/RGB_095: LED079.2, LED080.4
/RGB_096: LED078.2, LED079.4
/RGB_097: LED078.4, LED098.2
/RGB_098: LED098.4, LED099.2
/RGB_099: LED099.4, LED100.2
/RGB_100: LED100.4, LED101.2
/RGB_101: LED101.4, LED102.2
/RGB_102: LED102.4, LED103.2
/RGB_103: LED103.4, LED104.2
/RGB_104: LED104.4, LED105.2
/RGB_105: LED105.4, LED106.2
/RGB_106: LED106.4, LED107.2
/RGB_107: LED107.4, LED108.2
/RGB_108: LED108.4, LED109.2
/RGB_109: LED109.4, LED110.2
/RGB_110: LED110.4, LED111.2
/RGB_111: LED111.4, LED117.2
/RGB_112: LED116.2, LED117.4
/RGB_113: LED115.2, LED116.4
/RGB_114: LED114.2, LED115.4
/RGB_115: LED113.2, LED114.4
/RGB_116: LED112.2, LED113.4
/RGB_117: LED112.4, LED118.2
/RGB_118: LED118.4, LED119.2
/RGB_119: LED119.4, LED120.2
/RGB_120: LED120.4, LED121.2
/RGB_BUFFERED: R1.1, TP6.1, U2.4
/RGB_DATA: J2.9, R3.1, U2.2
/ROW0: J1.1, SW001.1, SW002.1, SW003.1, SW004.1, SW005.1, SW006.1, SW007.1, SW008.1, SW009.1, SW010.1, SW011.1, SW012.1, SW013.1, SW014.1, SW015.1, SW016.1
/ROW1: J1.2, SW017.1, SW018.1, SW019.1, SW020.1, SW021.1, SW022.1, SW023.1, SW024.1, SW025.1, SW026.1, SW027.1, SW028.1, SW029.1, SW030.1, SW031.1, SW032.1
/ROW2: J1.4, SW033.1, SW034.1, SW035.1, SW036.1, SW037.1, SW038.1, SW039.1, SW040.1, SW041.1, SW042.1, SW043.1, SW044.1, SW045.1, SW046.1, SW047.1, SW048.1
/ROW3: J1.5, SW049.1, SW050.1, SW051.1, SW052.1, SW053.1, SW054.1, SW055.1, SW056.1, SW057.1, SW058.1, SW059.1, SW060.1, SW061.1, SW062.1, SW063.1, SW064.1
/ROW4: J1.6, SW065.1, SW066.1, SW067.1, SW068.1, SW069.1, SW070.1, SW071.1, SW072.1, SW073.1, SW074.1, SW075.1, SW076.1, SW077.1, SW078.1, SW079.1, SW080.1
/ROW5: J1.7, SW081.1, SW082.1, SW083.1, SW084.1, SW085.1, SW086.1, SW087.1, SW088.1, SW089.1, SW090.1, SW091.1, SW092.1, SW093.1, SW094.1, SW095.1, SW096.1
/ROW6: J1.9, SW097.1, SW098.1, SW099.1, SW100.1, SW101.1, SW102.1, SW103.1, SW104.1, SW105.1, SW106.1, SW107.1, SW108.1, SW109.1, SW110.1, SW111.1, SW112.1
/ROW7: J1.10, SW113.1, SW114.1, SW115.1, SW116.1, SW117.1

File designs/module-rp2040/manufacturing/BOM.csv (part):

reference,value,footprint,x_mm,y_mm,side,Manufacturer,MPN,LCSC,Key
U1,Waveshare RP2040-Plus 4MB,Waveshare_RP2040_Plus,425.7675,13.39,F,,,,
J1,M20-7862042,Harwin_M20_7862042,425.7675,4.5,B,Harwin,M20-7862042,C5379059,
J2,M20-7862042,Harwin_M20_7862042,425.7675,22.28,B,Harwin,M20-7862042,C5379059,
SW001,CPG151101S11-16,HanElectricity_CPG151101S11-16,33.3375,9.525,B,HanElectricity,CPG151101S11-16,C41430893,Esc
D001,1N4148W,D_SOD123,33.3375,1.2750000000000004,B,Semtech,1N4148W,C81598,
LED001,SK6812MINI-E C5149201,MINI_E,33.3375,14.605,B,OPSCO Optoelectronics,SK6812MINI-E,C5149201,
C101,100nF 50V X7R,C_0805,39.137499999999996,14.605,B,YAGEO,CC0805KRX7R9BB104,C49678,
SW002,CPG151101S11-16,HanElectricity_CPG151101S11-16,71.4375,9.525,B,HanElectricity,CPG151101S11-16,C41430893,F1
D002,1N4148W,D_SOD123,71.4375,1.2750000000000004,B,Semtech,1N4148W,C81598,
LED002,SK6812MINI-E C5149201,MINI_E,71.4375,14.605,B,OPSCO Optoelectronics,SK6812MINI-E,C5149201,
C102,100nF 50V X7R,C_0805,77.2375,14.605,B,YAGEO,CC0805KRX7R9BB104,C49678,
SW003,CPG151101S11-16,HanElectricity_CPG151101S11-16,90.4875,9.525,B,HanElectricity,CPG151101S11-16,C41430893,F2
D003,1N4148W,D_SOD123,90.4875,1.2750000000000004,B,Semtech,1N4148W,C81598,
LED003,SK6812MINI-E C5149201,MINI_E,90.4875,14.605,B,OPSCO Optoelectronics,SK6812MINI-E,C5149201,
C103,100nF 50V X7R,C_0805,96.2875,14.605,B,YAGEO,CC0805KRX7R9BB104,C49678,
SW004,CPG151101S11-16,HanElectricity_CPG151101S11-16,109.53750000000001,9.525,B,HanElectricity,CPG151101S11-16,C41430893,F3
D004,1N4148W,D_SOD123,109.53750000000001,1.2750000000000004,B,Semtech,1N4148W,C81598,
LED004,SK6812MINI-E C5149201,MINI_E,109.53750000000001,14.605,B,OPSCO Optoelectronics,SK6812MINI-E,C5149201,
C104,100nF 50V X7R,C_0805,115.3375,14.605,B,YAGEO,CC0805KRX7R9BB104,C49678,
SW005,CPG151101S11-16,HanElectricity_CPG151101S11-16,128.5875,9.525,B,HanElectricity,CPG151101S11-16,C41430893,F4
D005,1N4148W,D_SOD123,128.5875,1.2750000000000004,B,Semtech,1N4148W,C81598,
LED005,SK6812MINI-E C5149201,MINI_E,128.5875,14.605,B,OPSCO Optoelectronics,SK6812MINI-E,C5149201,
C105,100nF 50V X7R,C_0805,134.38750000000002,14.605,B,YAGEO,CC0805KRX7R9BB104,C49678,
SW006,CPG151101S11-16,HanElectricity_CPG151101S11-16,157.1625,9.525,B,HanElectricity,CPG151101S11-16,C41430893,F5
D006,1N4148W,D_SOD123,157.1625,1.2750000000000004,B,Semtech,1N4148W,C81598,
LED006,SK6812MINI-E C5149201,MINI_E,157.1625,14.605,B,OPSCO Optoelectronics,SK6812MINI-E,C5149201,
C106,100nF 50V X7R,C_0805,162.9625,14.605,B,YAGEO,CC0805KRX7R9BB104,C49678,
SW007,CPG151101S11-16,HanElectricity_CPG151101S11-16,176.2125,9.525,B,HanElectricity,CPG151101S11-16,C41430893,F6
D007,1N4148W,D_SOD123,176.2125,1.2750000000000004,B,Semtech,1N4148W,C81598,
LED007,SK6812MINI-E C5149201,MINI_E,176.2125,14.605,B,OPSCO Optoelectronics,SK6812MINI-E,C5149201,
C107,100nF 50V X7R,C_0805,182.01250000000002,14.605,B,YAGEO,CC0805KRX7R9BB104,C49678,
SW008,CPG151101S11-16,HanElectricity_CPG151101S11-16,195.26250000000002,9.525,B,HanElectricity,CPG151101S11-16,C41430893,F7
D008,1N4148W,D_SOD123,195.26250000000002,1.2750000000000004,B,Semtech,1N4148W,C81598,
LED008,SK6812MINI-E C5149201,MINI_E,195.26250000000002,14.605,B,OPSCO Optoelectronics,SK6812MINI-E,C5149201,
C108,100nF 50V X7R,C_0805,201.06250000000003,14.605,B,YAGEO,CC0805KRX7R9BB104,C49678,
SW009,CPG151101S11-16,HanElectricity_CPG151101S11-16,214.3125,9.525,B,HanElectricity,CPG151101S11-16,C41430893,F8
D009,1N4148W,D_SOD123,214.3125,1.2750000000000004,B,Semtech,1N4148W,C81598,
LED009,SK6812MINI-E C5149201,MINI_E,214.3125,14.605,B,OPSCO Optoelectronics,SK6812MINI-E,C5149201,
C109,100nF 50V X7R,C_0805,220.1125,14.605,B,YAGEO,CC0805KRX7R9BB104,C49678,
SW010,CPG151101S11-16,HanElectricity_CPG151101S11-16,242.88750000000002,9.525,B,HanElectricity,CPG151101S11-16,C41430893,F9
D010,1N4148W,D_SOD123,242.88750000000002,1.2750000000000004,B,Semtech,1N4148W,C81598,
LED010,SK6812MINI-E C5149201,MINI_E,242.88750000000002,14.605,B,OPSCO Optoelectronics,SK6812MINI-E,C5149201,
C110,100nF 50V X7R,C_0805,248.68750000000003,14.605,B,YAGEO,CC0805KRX7R9BB104,C49678,
SW011,CPG151101S11-16,HanElectricity_CPG151101S11-16,261.9375,9.525,B,HanElectricity,CPG151101S11-16,C41430893,F10
D011,1N4148W,D_SOD123,261.9375,1.2750000000000004,B,Semtech,1N4148W,C81598,
LED011,SK6812MINI-E C5149201,MINI_E,261.9375,14.605,B,OPSCO Optoelectronics,SK6812MINI-E,C5149201,
C111,100nF 50V X7R,C_0805,267.7375,14.605,B,YAGEO,CC0805KRX7R9BB104,C49678,
SW012,CPG151101S11-16,HanElectricity_CPG151101S11-16,280.9875,9.525,B,HanElectricity,CPG151101S11-16,C41430893,F11
D012,1N4148W,D_SOD123,280.9875,1.2750000000000004,B,Semtech,1N4148W,C81598,
LED012,SK6812MINI-E C5149201,MINI_E,280.9875,14.605,B,OPSCO Optoelectronics,SK6812MINI-E,C5149201,
C112,100nF 50V X7R,C_0805,286.7875,14.605,B,YAGEO,CC0805KRX7R9BB104,C49678,
SW013,CPG151101S11-16,HanElectricity_CPG151101S11-16,300.0375,9.525,B,HanElectricity,CPG151101S11-16,C41430893,F12
D013,1N4148W,D_SOD123,300.0375,1.2750000000000004,B,Semtech,1N4148W,C81598,
LED013,SK6812MINI-E C5149201,MINI_E,300.0375,14.605,B,OPSCO Optoelectronics,SK6812MINI-E,C5149201,
C113,100nF 50V X7R,C_0805,305.83750000000003,14.605,B,YAGEO,CC0805KRX7R9BB104,C49678,
SW014,CPG151101S11-16,HanElectricity_CPG151101S11-16,323.85,9.525,B,HanElectricity,CPG151101S11-16,C41430893,PrtSc
D014,1N4148W,D_SOD123,323.85,1.2750000000000004,B,Semtech,1N4148W,C81598,
LED014,SK6812MINI-E C5149201,MINI_E,323.85,14.605,B,OPSCO Optoelectronics,SK6812MINI-E,C5149201,
C114,100nF 50V X7R,C_0805,329.65000000000003,14.605,B,YAGEO,CC0805KRX7R9BB104,C49678,
SW015,CPG151101S11-16,HanElectricity_CPG151101S11-16,342.90000000000003,9.525,B,HanElectricity,CPG151101S11-16,C41430893,Scroll Lock
D015,1N4148W,D_SOD123,342.90000000000003,1.2750000000000004,B,Semtech,1N4148W,C81598,
LED015,SK6812MINI-E C5149201,MINI_E,342.90000000000003,14.605,B,OPSCO Optoelectronics,SK6812MINI-E,C5149201,
C115,100nF 50V X7R,C_0805,348.70000000000005,14.605,B,YAGEO,CC0805KRX7R9BB104,C49678,
SW016,CPG151101S11-16,HanElectricity_CPG151101S11-16,361.95,9.525,B,HanElectricity,CPG151101S11-16,C41430893,Pause/Break
D016,1N4148W,D_SOD123,361.95,1.2750000000000004,B,Semtech,1N4148W,C81598,
LED016,SK6812MINI-E C5149201,MINI_E,361.95,14.605,B,OPSCO Optoelectronics,SK6812MINI-E,C5149201,
C116,100nF 50V X7R,C_0805,367.75,14.605,B,YAGEO,CC0805KRX7R9BB104,C49678,
SW017,CPG151101S11-16,HanElectricity_CPG151101S11-16,9.525,38.1,B,HanElectricity,CPG151101S11-16,C41430893,M1
D017,1N4148W,D_SOD123,9.525,29.85,B,Semtech,1N4148W,C81598,
LED017,SK6812MINI-E C5149201,MINI_E,9.525,43.18,B,OPSCO Optoelectronics,SK6812MINI-E,C5149201,
C117,100nF 50V X7R,C_0805,15.325,43.18,B,YAGEO,CC0805KRX7R9BB104,C49678,
SW018,CPG151101S11-16,HanElectricity_CPG151101S11-16,33.3375,38.1,B,HanElectricity,CPG151101S11-16,C41430893,~/`
D018,1N4148W,D_SOD123,33.3375,29.85,B,Semtech,1N4148W,C81598,
LED018,SK6812MINI-E C5149201,MINI_E,33.3375,43.18,B,OPSCO Optoelectronics,SK6812MINI-E,C5149201,
C118,100nF 50V X7R,C_0805,39.137499999999996,43.18,B,YAGEO,CC0805KRX7R9BB104,C49678,
SW019,CPG151101S11-16,HanElectricity_CPG151101S11-16,52.3875,38.1,B,HanElectricity,CPG151101S11-16,C41430893,!/1
D019,1N4148W,D_SOD123,52.3875,29.85,B,Semtech,1N4148W,C81598,
LED019,SK6812MINI-E C5149201,MINI_E,52.3875,43.18,B,OPSCO Optoelectronics,SK6812MINI-E,C5149201,
C119,100nF 50V X7R,C_0805,58.1875,43.18,B,YAGEO,CC0805KRX7R9BB104,C49678,
SW020,CPG151101S11-16,HanElectricity_CPG151101S11-16,71.4375,38.1,B,HanElectricity,CPG151101S11-16,C41430893,@/2
D020,1N4148W,D_SOD123,71.4375,29.85,B,Semtech,1N4148W,C81598,
LED020,SK6812MINI-E C5149201,MINI_E,71.4375,43.18,B,OPSCO Optoelectronics,SK6812MINI-E,C5149201,
C120,100nF 50V X7R,C_0805,77.2375,43.18,B,YAGEO,CC0805KRX7R9BB104,C49678,
SW021,CPG151101S11-16,HanElectricity_CPG151101S11-16,90.4875,38.1,B,HanElectricity,CPG151101S11-16,C41430893,#/3
D021,1N4148W,D_SOD123,90.4875,29.85,B,Semtech,1N4148W,C81598,
LED021,SK6812MINI-E C5149201,MINI_E,90.4875,43.18,B,OPSCO Optoelectronics,SK6812MINI-E,C5149201,
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
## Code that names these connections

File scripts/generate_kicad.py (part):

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    cap_index = {k["cap_ref"]: i for i,k in enumerate(leds)}
    corner_index = 0
    all_parts = parts + [dict(ref="#FLG01", kind="PowerFlag", value="PWR_FLAG", pins={"1":"GND"}),
                         dict(ref="#FLG02", kind="PowerFlag", value="PWR_FLAG", pins={"1":"FUSED_5V"}),
                         dict(ref="#FLG03", kind="PowerFlag", value="PWR_FLAG", pins={"1":"RAW_USB_5V"})]
    for part in all_parts:
        ref, kind = part["ref"], part["kind"]
        if ref.startswith("SW") or (ref.startswith("D") and ref[1:].isdigit()):
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    add_mechanics(board)
    for ref, net, x, y in TEST_POINTS:
        label = pcbnew.PCB_TEXT(board)
        label.SetText(ref+' '+{'RAW_USB_5V':'USB5V','LED_5V':'LED5V','RGB_BUFFERED':'RGB','LED_EN':'EN'}.get(net,net))
        label.SetPosition(mm(x,y-1.5)); label.SetLayer(pcbnew.B_SilkS); label.SetMirrored(True)
        label.SetTextSize(mm(.8,.8)); label.SetTextThickness(pcbnew.FromMM(.12)); board.Add(label)
    for k in keys:
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
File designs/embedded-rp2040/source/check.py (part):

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    for p in [19,57]:require(net('U1',p)=='GND',f'U1 ground/test {p}')
    require(net('U1',46)=='USB_DM' and net('U1',47)=='USB_DP','USB RP2040 pin order')
    for n,g in {**{i+2:i for i in range(8)},**{i+3:i for i in range(8,16)},**{i+11:i for i in range(16,22)},34:22,38:26}.items():
        require(net('U1',n)==(f'ROW{g}' if g<8 else f'COL{g-8:02d}' if g<23 else 'COL15'),f'GPIO mapping GP{g}')
    require(net('U1',39)=='RGB_DATA' and net('U1',40)=='LED_EN','LED GPIO mapping')
    for pin,n in {1:'QSPI_SS',2:'QSPI_SD1',3:'QSPI_SD2',4:'GND',5:'QSPI_SD0',6:'QSPI_SCLK',7:'QSPI_SD3',8:'3V3'}.items():require(net('U4',pin)==n,f'Flash pin {pin}')
    require('SOIC-8W_5.3x5.3' in str(fps['U4'].GetFPID().GetLibItemName()),'W25Q32JVSSIQ requires 208-mil SS package')
    for pin,n in {1:'RAW_USB_5V',2:'GND',3:'RAW_USB_5V',5:'3V3'}.items():require(net('U5',pin)==n,f'AP2112 pin {pin}')
    for p in ['A4','A9','B4','B9']:require(net('J1',p)=='RAW_USB_5V','Connector VBUS')
    for p in ['A1','A12','B1','B12','S1']:require(net('J1',p)=='GND','Connector ground')
    for ref,pin,name in [('R12',1,'CC1'),('R13',1,'CC2'),('J1','A5','CC1'),('J1','B5','CC2')]:require(net(ref,pin)==name,'Independent CC resistors')
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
